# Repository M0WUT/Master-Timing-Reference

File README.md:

Artefacts: https://m0wut.github.io/Master-Timing-Reference/

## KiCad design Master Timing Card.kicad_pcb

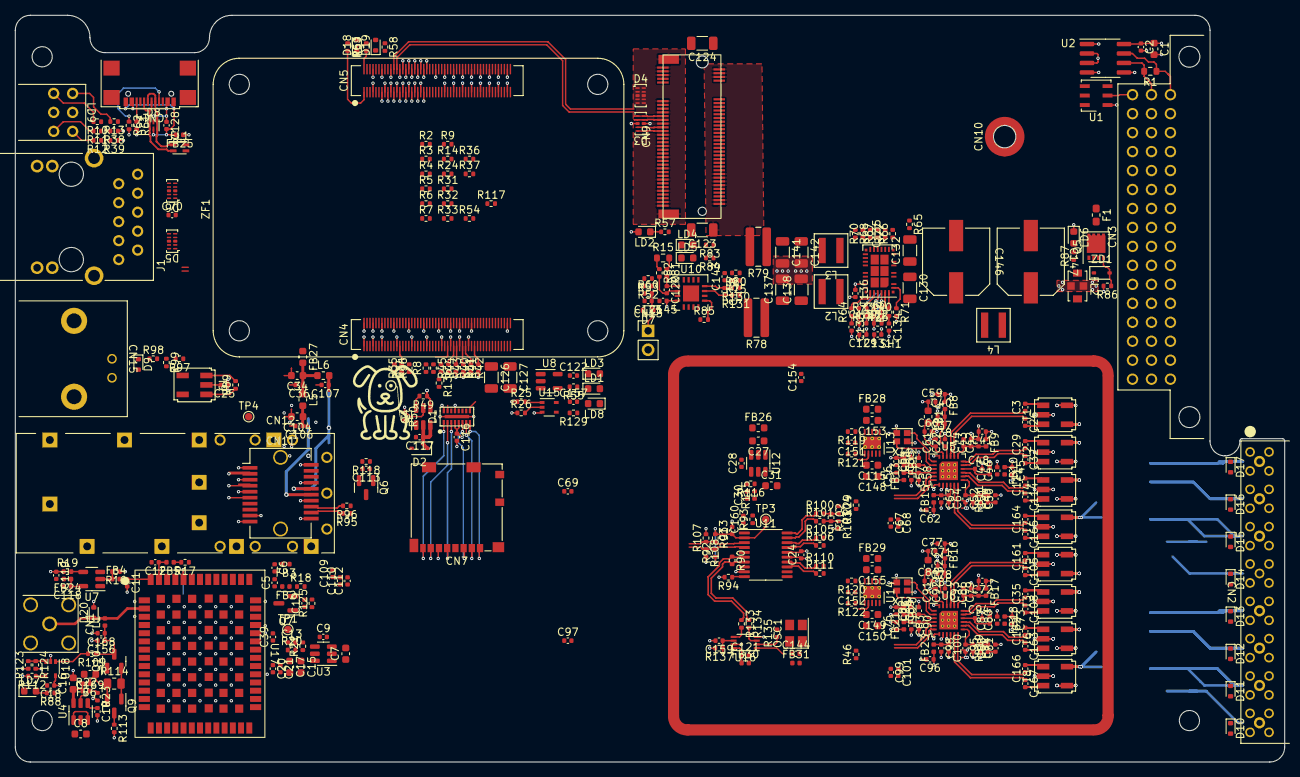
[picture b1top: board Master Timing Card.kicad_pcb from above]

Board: 4 copper layers, 170.0 x 100.0 mm, 418 parts (1 on the bottom side), 289 nets.

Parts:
C1, C7, C8, C15, C16, C17, C27, C31, C34, C104, C115, C148, C149, C150, C153, C155, C169: 10u; C_0603_1608Metric
C2, C3, C9, C10, C18, C19, C20, C21, C24, C25, C26, C28, C29, C32, C33, C35, C36, C38, C39, C40, C41, C43, C45, C47, C49, C51, C53, C55, C56, C58, C59, C61, C62, C64, C70, C71, C72, C73, C74, C75, C76, C77, C85, C86, C87, C88, C89, C90, C91, C96, C100, C105, C106, C107, C108, C111, C113, C114, C116, C117, C118, C121, C122, C125, C128, C135, C144, C145, C154, C156, C157, C159, C160, C161, C162, C163, C164, C165, C166, C167: 100n; C_0402_1005Metric
C5, C6, C11, C12, C67, C68, C69, C97, C99, C101, C109, C110, C112, C119: 100p; C_0402_1005Metric
C13, C30: 15p; C_0402_1005Metric
C22, C44, C48, C52, C92, C93, C94, C95, C168: 4n7; C_0402_1005Metric
C37, C42, C46, C50, C54, C57, C60, C63, C78, C79, C80, C81, C82, C83, C84, C98: 10u; C_0402_1005Metric
C120, C136, C143, C151, C152, C158: 1u; C_0402_1005Metric
C123, C124, C126, C127: 22u; C_1206_3216Metric
C129, C131: 10n; C_0402_1005Metric
C130, C132: 10u; C_1206_3216Metric
C133, C134: 220p; C_0402_1005Metric
C137, C138, C141, C142: 47u; C_1206_3216Metric
C139, C140: 10p; C_0402_1005Metric
C146, C147: 220u; Wurth_WCAP-HSG5_8x10.5mm_SM
CN1: CONSMA002-L-G; SMA_Linx_CONSMA002-L-G_Horizontal
CN2: Samtec GRF1-J-P-08-E-RA-TH1; Samtec_GRF1-J-P-08-E-RA-TH1
CN3: Amphenol 86093488613755E1LF; DIN41612_R_03x16_Receptacle_RA_Amphenol_86093488613755E1LF
CN4: Hirose_DF40C-100DS-0.4V
CN5: Hirose_DF40C-100DS-0.4V_pins-101-200
CN7: 104031-0811; microSD_HC_Molex_104031-0811
CN9: TE 1-2199230-6; TE_1-2199230-6
CN10: M2 x 2.5mm; Standoff_Wurth_9774025243R
CN11: UE75-A20-6000T; Amphenol_UE75-A20-6000T
CN12: U77-A1114-30L1; Amphenol_U77-A1114-30L1
CN13: Harwin M20-9990246; PinHeader_1x02_P2.54mm_Vertical
CN14: USB4110-GF-A; USB-C_GCT_USB4110-GF-A
CN15: 731385033; BNC_Molex_731385033
D1: ECLAMP2410P; Semtech_ECLAMP2410P
D2: 5V0; D_SOD-323
D3, D4, D5, D6: TPD4E05U06DQA
D7, D18, D19: 3V3; D_SOD-523
D8: USBLC6-2M6; TVS_ST_USBLC6-2M6
D9, D10, D11, D12, D13, D14, D15, D16, D17, D20: 5V0; D_SOD-523
F1: 1A; Fuse_0603_1608Metric_Pad1.05x0.95mm_HandSolder
FB2, FB3, FB4, FB5, FB6, FB8, FB9, FB10, FB11, FB12, FB13, FB15, FB16, FB17, FB18, FB19, FB20, FB21, FB23, FB24, FB25, FB30, FB31: 1k8; L_0402_1005Metric
FB14, FB22, FB26, FB27, FB28, FB29: 600R; L_0603_1608Metric
FL1: 90R; L_CommonMode_Wurth_WE-CNSW_0805
FL2: NFM31HK153R1H3; Murata_NFM31HK
H8: Logo_10mmx10mm
J1: Connector_RJ45_Magjack_Abracon_ARJM11D7-502-AB-EW2
L1: 47n; L_0402_1005Metric
L2, L3, L4: 2u2; Coilcraft_XEL4030
L5, L6: 1u0; L_0603_1608Metric
LAYOUT1, LAYOUT2, LAYOUT3: 2.7mm NPTH; MountingHole_2.7mm
LD1: Red; LED_0603_1608Metric
LD2, LD3, LD4, LD5, LD6, LD7, LD8: Green; LED_0603_1608Metric
LD9: WP130WCP_2EGW; Kingbright_WP130WCP_2EGW
OSC1: 10MHz; Crystal_SMD_3225-4Pin_3.2x2.5mm
Q4: onsemi FDC6330L; TSOT-23-6
Q5: TSM085P03CV RGG; PDFN33-8
Q6, Q7: DMN62D0U-7; SOT-23
Q9, Q10: MMBT2907A-7-F; SOT-23
R1: 120R; R_0603_1608Metric
R2, R3, R4, R31, R32, R35, R83, R84, R88, R117: 4k7; R_0402_1005Metric
R5, R6, R8, R9, R14, R24, R29, R33, R34, R36, R37, R46, R51, R58, R59, R60, R89, R90, R109, R136: 100R; R_0402_1005Metric
R7, R16, R17, R18, R19, R40, R41, R42, R43, R44, R45, R100, R101, R105, R106, R110, R111, R133, R134, R135: 33R; R_0402_1005Metric
R10, R11, R12, R13, R38, R39, R54, R55, R57, R113: 1k0; R_0402_1005Metric
R15: 150m; R_0603_1608Metric
R20, R22, R115, R124: 22k; R_0402_1005Metric
R21, R116: 13k; R_0402_1005Metric
R23: 7k5; R_0402_1005Metric
R25, R26, R49, R50, R66, R67, R86, R93, R112, R118, R123, R125, R129, R137: 10k; R_0402_1005Metric
R52, R53, R56, R63, R68, R70: 0R0; R_0402_1005Metric
R61, R62: 5k1; R_0402_1005Metric
R64, R69, R71, R76: 15k; R_0402_1005Metric
R65: 120k; R_0402_1005Metric
R72, R87: 47k; R_0402_1005Metric
R73: 160k; R_0402_1005Metric
R74: 30k; R_0402_1005Metric
R75, R80, R81, R82, R130, R131: 6R8; R_0402_1005Metric
R77, R85: 100k; R_0402_1005Metric
R78, R79: 56m; R_1020_2550Metric
R91, R92: 130R; R_0402_1005Metric
R94: 475R; R_0402_1005Metric
R95, R96: 10R; R_0402_1005Metric
R97, R98: 20R; R_0402_1005Metric
R99: 51R; R_0402_1005Metric
R102: 140R; R_0402_1005Metric
R103, R104: 180R; R_0402_1005Metric
R107, R108: 82R; R_0402_1005Metric
R114: 10R; R_0805_2012Metric
R119, R120: 330R; R_0402_1005Metric
R121, R122: 18k; R_0402_1005Metric
SH1: MS585-10F; Shield_Masach_MS585-10_58.2x49.4x4.7mm_SMD
T1, T2, T3, T4, T5, T6, T7, T8, T9: TC2-72T+; MiniCircuits_AT1521
TP1, TP3, TP4, TP5: TestPoint_Pad_D1.0mm
U1: DS2431P+; TSOC-6_3.76x3.94mm_P1.27mm
U2: Analog MAX3483ESA+; SOIC-8_3.9x4.9mm_P1.27mm
U3, U4, U12: TI TPS79301DBV; SOT-23-6
U5, U6: RC32504A000GNK#BB0; Renesas_QFN-24-1EP_4x4mm_P0.5mm_EP2.5x2.5mm_ThermalVias
U7, U8: SN74LVC1G125DBV; SOT-23-5
U9: Analog LT8650SEV#PBF; LQFN-32(28)-6EP_6x4mm_P0.5mm_EP1.1x1.33mm
U10: INA3221AIRGV; Texas_VQFN-16-1EP_RGV0016A
U11: SY75576LKY; TSSOP-20_4.4x6.5mm_P0.65mm
U13, U14: LT3045IDD#PBF; DFN-10-1EP_3x3mm_P0.5mm_EP1.65x2.38mm_ThermalVias
U15: SN74LVC1G02DCK; SOT-353_SC-70-5
U16: SN74LVC2G157DCU; VSSOP-8_2.3x2mm_P0.5mm
U17: ZED-F9T-10B; uBlox_ZED
U18: TLV7031DCK; SOT-353_SC-70-5
XT1, XT2: 60MHz; Crystal_SMD_2016-4Pin_2.0x1.6mm
ZD1: 15V; D_SOD-323
ZF1: CM4004016; Raspberry-Pi-4-Compute-Module

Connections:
0V: C1.2, C2.2, C5.2, C6.2, C7.2, C8.2, C9.2, C10.2, C11.2, C12.2, C15.2, C16.2, C17.2, C18.2, C19.2, C20.2, C21.2, C22.2, C24.2, C25.1, C27.2, C28.2, C31.2, C33.2, C34.2, C36.2, C37.2, C38.2, C39.2, C40.2, C41.2, C42.2, C43.2, C44.2, C45.2, C46.2, C47.2, C48.2, C49.2, C50.2, C51.2, C52.2, C53.2, C54.2, C55.2, C56.2, C57.2, C58.2, C59.2, C60.2, C61.2, C62.2, C63.2, C64.2, C67.2, C68.2, C69.2, C70.2, C71.2, C72.2, C73.2, C74.2, C75.2, C76.2, C77.2, C78.2, C79.2, C80.2, C81.2, C82.2, C83.2, C84.2, C85.2, C86.2, C87.2, C88.2, C89.2, C90.2, C91.2, C92.2, C93.2, C94.2, C95.2, C96.2, C97.2, C98.2, C99.2, C100.2, C101.2, C104.2, C106.2, C107.2, C109.2, C110.2, C112.2, C113.2, C115.2, C116.2, C117.2, C118.2, C119.2, C121.2, C122.2, C123.2, C124.2, C125.2, C126.2, C127.2, C129.2, C130.2, C131.2, C132.2, C133.2, C134.2, C135.2, C136.2, C137.2, C138.2, C141.2, C142.2, C144.2, C145.2, C146.2, C147.2, C148.2, C149.2, C150.2, C151.2, C152.2, C153.2, C154.2, C155.2, C156.2, C157.2, C159.2, C160.2, C168.2, C169.2, CN1.2 (Ext), CN2.SH1 (Ext), CN2.SH2 (Ext), CN2.SH3 (Ext), CN2.SH4 (Ext), CN2.SH5 (Ext), CN2.SH6 (Ext), CN2.SH7 (Ext), CN2.SH8 (Ext), CN3.a16, CN4.1 (GND), CN4.2 (GND), CN4.7 (GND), CN4.8 (GND), CN4.13 (GND), CN4.14 (GND), CN4.22 (GND), CN4.23 (GND), CN4.32 (GND), CN4.33 (GND), CN4.42 (GND), CN4.43 (GND), CN4.52 (GND), CN4.53 (GND), CN4.59 (GND), CN4.60 (GND), CN4.65 (GND), CN4.66 (GND), CN4.71 (GND), CN4.74 (GND), CN4.98 (GND), CN5.107 (GND), CN5.108 (GND), CN5.113 (GND), CN5.114 (GND), CN5.115 (CAM1_D0_N), CN5.117 (CAM1_D0_P), CN5.119 (GND), CN5.120 (GND), CN5.121 (CAM1_D1_N), CN5.123 (CAM1_D1_P), CN5.125 (GND), CN5.126 (GND), CN5.127 (CAM1_C_N), CN5.128 (CAM0_D0_N), CN5.129 (CAM1_C_P), CN5.130 (CAM0_D0_P), CN5.131 (GND), CN5.132 (GND), CN5.133 (CAM1_D2_N), CN5.134 (CAM0_D1_N), CN5.135 (CAM1_D2_P), CN5.136 (CAM0_D1_P), CN5.137 (GND), CN5.138 (GND), CN5.139 (CAM1_D3_N), CN5.140 (CAM0_C_N), CN5.141 (CAM1_D3_P), CN5.142 (CAM0_C_P), CN5.144 (GND), CN5.150 (GND), CN5.155 (GND), CN5.156 (GND), CN5.161 (GND), CN5.162 (GND), CN5.167 (GND), CN5.168 (GND), CN5.173 (GND), CN5.174 (GND), CN5.179 (GND), CN5.180 (GND), CN5.185 (GND), CN5.186 (GND), CN5.191 (GND), CN5.192 (GND), CN5.197 (GND), CN5.198 (GND), CN7.6 (VSS), CN7.9 (DET_B), CN7.10 (DET_A), CN7.11 (SHIELD), CN9.1 (GND), CN9.3 (GND), CN9.9 (GND), CN9.15 (GND), CN9.21 (GND), CN9.27 (GND), CN9.33 (GND), CN9.39 (GND), CN9.45 (GND), CN9.51 (GND), CN9.57 (GND), CN9.71 (GND), CN9.73 (GND), CN9.75 (GND), CN9.76 (MNT), CN10.1, CN11.1 (VeeT), CN11.9 (VeeR), CN11.10 (VeeR), CN11.11 (VeeR), CN11.14 (VeeR), CN11.17 (VeeT), CN11.20 (VeeT), CN12.1, CN13.2, CN14.SH (SHIELD), CN15.2 (Ext), D1.17 (0V), D2.2 (A), D3.3, D3.8, D4.3, D4.8, D5.3, D5.8, D6.3, D6.8, D7.2 (A), D9.2 (A), D10.2 (A), D11.2 (A), D12.2 (A), D13.2 (A), D14.2 (A), D15.2 (A), D16.2 (A), D17.2 (A), D18.2 (A), D19.2 (A), D20.2 (A), FB25.1, FL2.2, LD4.1 (K), LD5.1 (K), LD6.1 (K), LD7.1 (K), LD8.1 (K), LD9.2, LD9.5, OSC1.1 (GND), OSC1.2 (GND), Q4.1 (S1), Q6.2 (S), Q7.2 (S), R21.2, R23.2, R50.2, R52.1, R53.1, R56.2, R61.2, R62.2, R63.1, R66.2, R67.2, R70.2, R71.2, R74.2, R76.2, R86.2, R93.2, R94.2, R99.2, R103.2, R104.1, R107.2, R108.2, R113.2, R116.2, R118.2, R119.2, R120.2, R121.2, R122.2, R124.2, R125.2, R137.2, SH1.1, T1.2, T1.4, T2.2, T2.6, T3.2, T3.6, T4.2, T4.6, T5.2, T5.4, T6.2, T6.6, T7.2, T7.6, T8.2, T8.6, T9.6, U1.1 (GND), U2.5 (GND), U3.2 (GND), U4.2 (GND), U5.25 (VSS), U6.25 (VSS), U7.1 (~OE), U7.3 (-), U8.1 (~OE), U8.3 (-), U9.2 (GND), U9.10 (GND), U9.33 (GND), U9.34 (GND), U9.35 (GND), U9.36 (GND), U9.37 (GND), U9.38 (GND), U9.MNT, U10.3 (GND), U10.5 (A0), U10.17 (PAD), U11.9 (GND), U11.16 (GND), U12.2 (GND), U13.8 (GND), U13.11 (GND), U14.8 (GND), U14.11 (GND), U15.3 (0V), U16.4 (GND), U16.7 (~G), U17.1 (GND), U17.3 (GND), U17.12 (GND), U17.14 (GND), U17.32 (GND), U17.37 (GND), U17.38 (V_USB), U17.41 (GND), U17.48 (GND), U17.55 (MNT), U18.2 (V-), XT1.2, XT1.4, XT2.2, XT2.4
1V8: CN4.88 (+1.8v_(Output)), CN4.90 (+1.8v_(Output)), FB24.2
3V3: C1.1, C2.1, C18.1, C62.1, C96.1, C116.1, C122.1, C145.1, C157.1, CN4.78 (GPIO_VREF(1.8v/3.3v_Input)), D1.4 (RUP1), D1.5 (VDD), D1.13 (RUP3), FB15.1, FB23.1, FB27.1, FB30.2, FB31.2, LD1.2 (A), LD2.2 (A), LD3.2 (A), Q4.4 (S2), R2.1, R3.1, R4.1, R15.2, R25.1, R26.1, R31.1, R32.1, R35.1, R38.1, R39.1, R49.1, R77.1, R81.1, R85.1, R117.1, R123.1, U2.8 (VCC), U8.5 (+), U10.4 (VS), U10.16 (VPU), U15.5 (VCC), U18.5 (V+)
3V3_PCIE: C123.1, C124.1, C140.1, CN9.2 (3.3V), CN9.4 (3.3V), CN9.12 (3.3V), CN9.14 (3.3V), CN9.16 (3.3V), CN9.18 (3.3V), CN9.70 (3.3V), CN9.72 (3.3V), CN9.74 (3.3V), R72.1, R79.2, R80.1, R83.1
5V0_PI: C7.1, C8.1, C126.1, C127.1, C139.1, CN4.77 (+5v_(Input)), CN4.79 (+5v_(Input)), CN4.81 (+5v_(Input)), CN4.83 (+5v_(Input)), CN4.85 (+5v_(Input)), CN4.87 (+5v_(Input)), FB26.1, FB28.1, FB29.1, R73.1, R78.2, R84.1, R131.1, U3.1 (IN), U3.3 (EN), U4.1 (IN), U4.3 (EN)
/CM4 Interfaces/ETHA_N: CN4.10 (Ethernet_Pair0_N), D5.2, D5.9 (NC), J1.2
/CM4 Interfaces/ETHA_P: CN4.12 (Ethernet_Pair0_P), D5.1, D5.10 (NC), J1.1
/CM4 Interfaces/ETHB_N: CN4.6 (Ethernet_Pair1_N), D5.5, D5.6 (NC), J1.4
/CM4 Interfaces/ETHB_P: CN4.4 (Ethernet_Pair1_P), D5.4, D5.7 (NC), J1.3
/CM4 Interfaces/ETHC_N: CN4.9 (Ethernet_Pair2_N), D6.2, D6.9 (NC), J1.8
/CM4 Interfaces/ETHC_P: CN4.11 (Ethernet_Pair2_P), D6.1, D6.10 (NC), J1.7
/CM4 Interfaces/ETHD_N: CN4.5 (Ethernet_Pair3_N), D6.5, D6.6 (NC), J1.10
/CM4 Interfaces/ETHD_P: CN4.3 (Ethernet_Pair3_P), D6.4, D6.7 (NC), J1.9
/CM4 Interfaces/PTP_PPS: C119.1, CN4.16 (Ethernet_SYNC_IN(1.8v)), R19.1
/CM4 Interfaces/SD_CLK: D1.14 (CLK_OUT), R45.2
/CM4 Interfaces/SD_CMD: D1.11 (CMD_OUT), R44.2
/CM4 Interfaces/SD_DAT0: D1.15 (DAT0_OUT), R40.2
/CM4 Interfaces/SD_DAT1: D1.16 (DAT1_OUT), R41.2
/CM4 Interfaces/SD_DAT2: D1.9 (DAT2_OUT), R42.2
/CM4 Interfaces/SD_DAT3: D1.10 (DAT3_OUT), R43.2
/CM4 Interfaces/SD_PWR_ON: Q4.5 (G1), R50.1, R51.1
/CM4 Interfaces/VDD_SD: C117.1, CN7.4 (VDD), D2.1 (K), Q4.2 (D2), Q4.3 (D2)
/CM4 Interfaces/~ETH_ACT: CN4.15 (Ethernet_nLED3(3.3v)), J1.L2
/CM4 Interfaces/~ETH_LINK: CN4.17 (Ethernet_nLED2(3.3v)), J1.L4
/GPS/CLK_SEL: C159.1, R24.2, R137.1, U16.6 (~A/B)
/GPS/GNSS_CLK_M: C12.1, FB5.2, U17.53 (TIMEPULSE)
/GPS/GNSS_PPS: CN4.49 (GPIO18), R16.1
/GPS/GNSS_PPS_M: C11.1, FB4.2, U17.54 (TIMEPULSE2)
/GPS/GNSS_RESET: C19.1, Q7.1 (G), R14.2, R125.1
/GPS/GNSS_RX: CN4.34 (GPIO5), R18.2
/GPS/GNSS_TX: CN4.54 (GPIO4), FB3.1
/GPS/REF_CLK_N: R90.2, R134.1, U11.7 (IN2_N)
/GPS/REF_CLK_P: R90.1, R133.1, U11.6 (IN2_P)
/GPS/~ANT_SHORT: R112.2, U17.6 (ANT_SHORT_N)
/PLL and SFP/CLKA_N: R101.1, U11.19 (CLKA_N)
/PLL and SFP/CLKA_P: R100.1, U11.20 (CLKA_P)
/PLL and SFP/CLKB_N: R106.1, U11.17 (CLKB_N)
/PLL and SFP/CLKB_P: R105.1, U11.18 (CLKB_P)
/PLL and SFP/CLKC_N: R111.1, U11.13 (CLKC_N)
/PLL and SFP/CLKC_P: R110.1, U11.14 (CLKC_P)
/PLL and SFP/CLKD_N: R89.2, T9.1, U11.11 (CLKD_N)
/PLL and SFP/CLKD_P: R89.1, T9.3, U11.12 (CLKD_P)
/PLL and SFP/CLK_SEL: C160.1, R93.1, R136.2, U11.1 (SEL)
/PLL and SFP/Frequency Synthesiser 1/1V8_PLL: C40.1, C41.1, C45.1, C49.1, C53.1, C56.1, C59.1, C115.1, C148.1, FB8.1, FB9.1, FB10.1, FB11.1, FB12.1, FB13.1, FB14.1, U13.9 (OUTS), U13.10 (OUT)
/PLL and SFP/Frequency Synthesiser 1/1V8_VDDA: C60.1, C61.1, FB14.2, U5.23 (VDDA)
/PLL and SFP/Frequency Synthesiser 1/1V8_VDDO0: C22.1, C37.1, C38.1, FB8.2, U5.22 (VDDO0)
/PLL and SFP/Frequency Synthesiser 1/1V8_VDDO1: C42.1, C43.1, C44.1, FB9.2, U5.19 (VDDO1)
/PLL and SFP/Frequency Synthesiser 1/1V8_VDDO2: C46.1, C47.1, C48.1, FB10.2, U5.16 (VDDO2)
/PLL and SFP/Frequency Synthesiser 1/1V8_VDDO3: C50.1, C51.1, C52.1, FB11.2, U5.13 (VDDO3)
/PLL and SFP/Frequency Synthesiser 1/1V8_VDDREF: C57.1, C58.1, FB13.2, U5.4 (VDDREF)
/PLL and SFP/Frequency Synthesiser 1/1V8_VDDXO: C54.1, C55.1, FB12.2, U5.3 (VDDXO)
/PLL and SFP/Frequency Synthesiser 1/3V3_VDDD: C63.1, C64.1, FB15.2, U5.10 (VDDD)
/PLL and SFP/Frequency Synthesiser 1/RF1_N: C3.1, U5.21 (OUT0_N)
/PLL and SFP/Frequency Synthesiser 1/RF1_P: C26.1, U5.20 (OUT0_P)
/PLL and SFP/Frequency Synthesiser 1/RF2_N: C32.1, U5.17 (OUT1_N)
/PLL and SFP/Frequency Synthesiser 1/RF2_P: C29.1, U5.18 (OUT1_P)
/PLL and SFP/Frequency Synthesiser 1/RF3_N: C114.1, U5.14 (OUT2_N)
/PLL and SFP/Frequency Synthesiser 1/RF3_P: C111.1, U5.15 (OUT2_P)
/PLL and SFP/Frequency Synthesiser 1/RF4_N: C165.1, U5.11 (OUT3_N)
/PLL and SFP/Frequency Synthesiser 1/RF4_P: C164.1, U5.12 (OUT3_P)
/PLL and SFP/Frequency Synthesiser 1/VIN: C153.1, FB28.2, U13.1 (IN), U13.2 (IN), U13.3 (EN/UV), U13.6 (PGFB)
/PLL and SFP/Frequency Synthesiser 1/~PLL_LOCK_OD: R25.2, R29.2, U15.1
/PLL and SFP/Frequency Synthesiser 2/1V8_PLL: C71.1, C72.1, C73.1, C74.1, C75.1, C76.1, C77.1, C149.1, C150.1, FB16.1, FB17.1, FB18.1, FB19.1, FB20.1, FB21.1, FB22.1, U14.9 (OUTS), U14.10 (OUT)
/PLL and SFP/Frequency Synthesiser 2/1V8_VDDA: C84.1, C91.1, FB22.2, U6.23 (VDDA)
/PLL and SFP/Frequency Synthesiser 2/1V8_VDDO0: C78.1, C85.1, C92.1, FB16.2, U6.22 (VDDO0)
/PLL and SFP/Frequency Synthesiser 2/1V8_VDDO1: C79.1, C86.1, C93.1, FB17.2, U6.19 (VDDO1)
/PLL and SFP/Frequency Synthesiser 2/1V8_VDDO2: C80.1, C87.1, C94.1, FB18.2, U6.16 (VDDO2)
/PLL and SFP/Frequency Synthesiser 2/1V8_VDDO3: C81.1, C88.1, C95.1, FB19.2, U6.13 (VDDO3)
/PLL and SFP/Frequency Synthesiser 2/1V8_VDDREF: C83.1, C90.1, FB21.2, U6.4 (VDDREF)
/PLL and SFP/Frequency Synthesiser 2/1V8_VDDXO: C82.1, C89.1, FB20.2, U6.3 (VDDXO)
/PLL and SFP/Frequency Synthesiser 2/3V3_VDDD: C98.1, C100.1, FB23.2, U6.10 (VDDD)
/PLL and SFP/Frequency Synthesiser 2/RF1_N: C161.1, U6.21 (OUT0_N)
/PLL and SFP/Frequency Synthesiser 2/RF1_P: C105.1, U6.20 (OUT0_P)
/PLL and SFP/Frequency Synthesiser 2/RF2_N: C108.1, U6.17 (OUT1_N)
/PLL and SFP/Frequency Synthesiser 2/RF2_P: C35.1, U6.18 (OUT1_P)
/PLL and SFP/Frequency Synthesiser 2/RF3_N: C163.1, U6.14 (OUT2_N)
/PLL and SFP/Frequency Synthesiser 2/RF3_P: C162.1, U6.15 (OUT2_P)
/PLL and SFP/Frequency Synthesiser 2/RF4_N: C167.1, U6.11 (OUT3_N)
/PLL and SFP/Frequency Synthesiser 2/RF4_P: C166.1, U6.12 (OUT3_P)
/PLL and SFP/Frequency Synthesiser 2/VIN: C155.1, FB29.2, U14.1 (IN), U14.2 (IN), U14.3 (EN/UV), U14.6 (PGFB)
/PLL and SFP/Frequency Synthesiser 2/~PLL_LOCK_OD: R26.2, R46.2, U15.2
/PLL and SFP/PLL1_CLK_N: R106.2, U5.6 (CLKIN_N)
/PLL and SFP/PLL1_CLK_P: R105.2, U5.5 (CLKIN_P)
/PLL and SFP/PLL1_SCL: C67.1, CN4.56 (GPIO3), R3.2, U5.8 (SCLK)
/PLL and SFP/PLL1_SDA: C68.1, CN4.58 (GPIO2), R2.2, U5.9 (SDIO)
/PLL and SFP/PLL2_CLK_N: R111.2, U6.6 (CLKIN_N)
/PLL and SFP/PLL2_CLK_P: R110.2, U6.5 (CLKIN_P)
/PLL and SFP/PLL2_SCL: C99.1, C110.1, CN4.37 (GPIO7), CN11.5 (MOD_DEF1/SCL), R32.2, U6.8 (SCLK), U10.6 (SCL)
/PLL and SFP/PLL2_SDA: C101.1, C112.1, CN4.30 (GPIO6), CN11.4 (MOD_DEF2/SDA), R31.2, U6.9 (SDIO), U10.7 (SDA)
/PLL and SFP/PLL_LOCK: CN4.27 (GPIO20), R129.2, U15.4
/PLL and SFP/PLL_OE: C69.1, C97.1, R5.2, U5.7 (OE/~CS), U6.7 (OE/~CS)
/PLL and SFP/REFCLK_R_N: CN11.13 (RD+), R96.2
/PLL and SFP/REFCLK_R_P: CN11.12 (RD-), R95.2
/PLL and SFP/SFP_LOS_OD: CN4.25 (GPIO21), CN11.8 (LOS), R35.2
/PLL and SFP/SFP_REFCLK_N: R92.2, R96.1, R108.1, U11.4 (IN1_N)
/PLL and SFP/SFP_REFCLK_P: R91.2, R95.1, R107.1, U11.3 (IN1_P)
/PLL and SFP/SFP_TX_DISABLE: C113.1, Q6.1 (G), R36.2, R118.1
/PLL and SFP/SFP_TX_FAULT_OD: CN4.40 (GPIO9), CN11.2 (TX_FAULT), R4.2
/PLL and SFP/SFP_TX_N: CN11.19 (TD-), R101.2, R102.2, R103.1
/PLL and SFP/SFP_TX_P: CN11.18 (TD+), R100.2, R102.1, R104.2
/PLL and SFP/VDD_MUX: C24.1, C30.1, C31.1, C33.1, C154.1, R91.1, R92.1, R115.1, TP3.1, U11.2 (VDDIN), U11.15 (VDD), U12.6 (OUT)
/PLL and SFP/~SFP_PRESENT: C109.1, CN4.39 (GPIO8), CN11.6 (MOD_DEF0/GND), R117.2
/Pi CM4 - GPIO/3V3_PCIE_EN: C135.1, R8.2, R67.1, U9.12 (EN2)
/Pi CM4 - GPIO/3V3_SENSE_N: C120.1, R81.2, U10.1 (IN3-)
/Pi CM4 - GPIO/3V3_SENSE_P: C120.2, R82.2, U10.2 (IN3+)
/Pi CM4 - GPIO/COMMS_GREEN: R6.1, R11.1
/Pi CM4 - GPIO/COMMS_RED: R9.1, R10.1
/Pi CM4 - GPIO/PCIE_PWR_GOOD: CN4.45 (GPIO24), R77.2, U9.15 (PG2)
/Pi CM4 - GPIO/PWR_CRITICAL: CN4.47 (GPIO23), R85.2, U10.9 (CRITICAL)
/Pi CM4 - GPIO/STATUS_GREEN: R12.1, R33.1
/Pi CM4 - GPIO/STATUS_RED: R13.1, R34.1
/Pi CM4 - HPIO/D_N: CN5.103 (USB2_N), FL1.2
/Pi CM4 - HPIO/D_P: CN5.105 (USB2_P), FL1.4
/Pi CM4 - HPIO/PCIE_PER0_N: CN5.118 (PCIe_RX_N), CN9.41 (PERn0), D3.1, D3.10 (NC)
/Pi CM4 - HPIO/PCIE_PER0_P: CN5.116 (PCIe_RX_P), CN9.43 (PERp0), D3.2, D3.9 (NC)
/Pi CM4 - HPIO/PCIE_PET0_N: CN5.124 (PCIe_TX_N), CN9.47 (PETn0), D3.4, D3.7 (NC)
/Pi CM4 - HPIO/PCIE_PET0_P: CN5.122 (PCIe_TX_P), CN9.49 (PETp0), D3.5, D3.6 (NC)
/Pi CM4 - HPIO/PCIE_REFCLK_N: CN5.112 (PCIe_CLK_N), CN9.53 (REFCLKn), D4.5, D4.6 (NC)
/Pi CM4 - HPIO/PCIE_REFCLK_P: CN5.110 (PCIe_CLK_P), CN9.55 (REFCLKp), D4.4, D4.7 (NC)
/Pi CM4 - HPIO/USB_N: CN14.A7 (DN1), CN14.B7 (DN2), D8.3, D8.4, FL1.1
/Pi CM4 - HPIO/USB_P: CN14.A6 (DP1), CN14.B6 (DP2), D8.1, D8.6, FL1.3
/Pi CM4 - HPIO/~PCIE_CLK_REQ: CN5.102 (PCIe_CLK_nREQ), R59.1
/Pi CM4 - HPIO/~PCIE_RST: CN9.50 (~PERST), D19.1 (K), R58.2
/Power Supplies/5V0_SENSE_N: C158.2, R131.2, U10.11 (IN1-)
/Power Supplies/5V0_SENSE_P: C158.1, R130.2, U10.12 (IN1+)
/Power Supplies/12V_DCDC: C130.1, C132.1, C146.1, L4.2, R65.1, U9.4 (VIN1), U9.5 (VIN1), U9.7 (VIN2), U9.8 (VIN2)
/Power Supplies/12V_F: F1.2, Q5.5, Q5.6, Q5.7, Q5.8
/Power Supplies/12V_FILT: C147.1, FL2.3, L4.1
/Power Supplies/12V_PROT: FL2.1, Q5.1, Q5.2, Q5.3, R87.1, ZD1.1 (K)
/Power Supplies/PCIE_SENSE_N: C143.2, R80.2, U10.14 (IN2-)
/Power Supplies/PCIE_SENSE_P: C143.1, R75.2, U10.15 (IN2+)
/Power Supplies/SW1: L2.1, U9.22 (SW1), U9.23 (SW1)
/Power Supplies/SW2: L3.1, U9.19 (SW2), U9.20 (SW2)
/RF1: CN2.1 (In), D17.1 (K), T1.6
/RF2: CN2.2 (In), D16.1 (K), T2.4
/RF3: CN2.3 (In), D15.1 (K), T4.4
/RF4: CN2.4 (In), D14.1 (K), T7.4
/RF5: CN2.5 (In), D13.1 (K), T5.6
/RF6: CN2.6 (In), D12.1 (K), T3.4
/RF7: CN2.7 (In), D11.1 (K), T6.4
/RF8: CN2.8 (In), D10.1 (K), T8.4
/RS485_A: CN3.b1, R1.2, U2.6 (A)
/RS485_B: CN3.a1, R1.1, U2.7 (B)
/RS485_RX: CN4.51 (GPIO15), U2.1 (RO)
/RS485_TX: R7.2, U2.4 (DI)
/RS485_~R/W: R37.2, U2.2 (~RE), U2.3 (DE)
unnamed: C3.2, T1.3
unnamed: C25.2, T9.2
unnamed: C26.2, T1.1
unnamed: C29.2, T2.3
unnamed: C32.2, T2.1
unnamed: C34.1, C36.1, FB27.2, L5.1, L6.1
unnamed: C35.2, T3.3
unnamed: C70.1, J1.5, J1.6
unnamed: C105.2, T5.1
unnamed: C108.2, T3.1
unnamed: C111.2, T4.3
unnamed: C114.2, T4.1
unnamed: C128.1, CN14.A4 (VBUS), CN14.A9 (VBUS), CN14.B4 (VBUS), CN14.B9 (VBUS), D8.5
unnamed: C128.2, CN14.A1 (GND), CN14.A12 (GND), CN14.B1 (GND), CN14.B12 (GND), D8.2, FB25.2
unnamed: C133.1, R64.1
unnamed: C134.1, R69.1
unnamed: C137.1, C138.1, L2.2, R78.1, R130.1
unnamed: C141.1, C142.1, L3.2, R75.1, R79.1
unnamed: C161.2, T5.3
unnamed: C162.2, T6.3
unnamed: C163.2, T6.1
unnamed: C164.2, T7.3
unnamed: C165.2, T7.1
unnamed: C166.2, T8.3
unnamed: C167.2, T8.1
unnamed: CN1.1 (In), D20.1 (K), L1.2, U17.2 (RF_IN)
unnamed: CN4.91 (BT_nDisable), R52.2
unnamed: CN4.20 (EEPROM_nWP), R56.1
unnamed: CN4.21 (PI_nLED_Activity), R54.2
unnamed: CN4.89 (WiFi_nDisable), R53.2
unnamed: CN4.95 (nPI_LED_PWR), U8.2
unnamed: CN4.93 (nRPIBOOT), R60.1
unnamed: CN4.57 (SD_CLK), R45.1
unnamed: CN4.62 (SD_CMD), R44.1
unnamed: CN4.63 (SD_DAT0), R40.1
unnamed: CN4.67 (SD_DAT1), R41.1
unnamed: CN4.69 (SD_DAT2), R42.1
unnamed: CN4.61 (SD_DAT3), R43.1
unnamed: CN4.75 (SD_PWR_ON), R51.2
unnamed: CN4.84 (+3.3v_(Output)), CN4.86 (+3.3v_(Output)), R15.1, R82.1
unnamed: CN4.44 (GPIO10), R6.2
unnamed: CN4.38 (GPIO11), R9.2
unnamed: CN4.31 (GPIO12), R33.2
unnamed: CN4.28 (GPIO13), R34.2
unnamed: CN4.55 (GPIO14), R7.1
unnamed: CN4.29 (GPIO16), R5.1
unnamed: CN4.50 (GPIO17), R37.1
unnamed: CN4.26 (GPIO19), R36.1
unnamed: CN4.46 (GPIO22), R8.1
unnamed: CN4.41 (GPIO25), R14.1
unnamed: CN4.24 (GPIO26), R24.1
unnamed: CN4.48 (GPIO27), R136.1
unnamed: CN5.109 (PCIe_nRST), R58.1
unnamed: CN5.101 (USB_OTG_ID), R63.2
unnamed: CN7.5 (CLK), D1.3 (CLK_IN)
unnamed: CN7.3 (CMD), D1.6 (CMD_IN)
unnamed: CN7.7 (DAT0), D1.2 (DAT0_IN)
unnamed: CN7.8 (DAT1), D1.1 (DAT1_IN)
unnamed: CN7.1 (DAT2), D1.8 (DAT2_IN)
unnamed: CN7.2 (DAT3/CD), D1.7 (DAT3_IN)
unnamed: CN9.52 (~CLKREQ), D18.1 (K), R59.2
unnamed: CN9.10 (~LED1), R57.2
unnamed: CN11.7 (RATE_SELECT), TP4.1
unnamed: CN11.3 (TX_DISABLE), Q6.3 (D)
unnamed: C104.1, C106.1, CN11.15 (VccR), L5.2
unnamed: C107.1, CN11.16 (VccT), L6.2
unnamed: C125.1, CN13.1, D7.1 (K), R60.2
unnamed: CN14.A5 (CC1), R62.1
unnamed: CN14.B5 (CC2), R61.1
unnamed: CN15.1 (In), D9.1 (K), R98.2
unnamed: FB2.1, R18.1
unnamed: FB4.1, R16.2, U7.2
unnamed: FB5.1, R17.2
unnamed: J1.L1, R39.2
unnamed: J1.L3, R38.2
unnamed: LD1.1 (K), R55.1
unnamed: LD2.1 (K), R57.1
unnamed: LD3.1 (K), R54.1
unnamed: LD4.2 (A), R83.2
unnamed: LD5.2 (A), R84.2
unnamed: LD6.2 (A), R87.2
unnamed: LD7.2 (A), R88.2
unnamed: LD8.2 (A), R129.1
unnamed: LD9.1, R13.2
unnamed: LD9.3, R12.2
unnamed: LD9.4, R10.2
unnamed: LD9.6, R11.2
unnamed: OSC1.3 (OUT), R135.2
unnamed: C144.1, FB31.1, OSC1.4 (VCC)
unnamed: Q4.6 (D1), R49.2
unnamed: Q7.3 (D), U17.49 (~RESET)
unnamed: C169.1, FB6.1, Q9.2 (E), R114.1
unnamed: Q9.3 (C), Q10.1 (B), R113.1
unnamed: C156.1, C168.1, L1.1, Q10.3 (C), R109.1
unnamed: Q9.1 (B), Q10.2 (E), R114.2
unnamed: R19.2, U7.4
unnamed: R55.2, U8.4
unnamed: R97.1, T9.4
unnamed: R97.2, R98.1, R99.1
unnamed: R112.1, U18.4
unnamed: CN3.c1, U1.2 (IO)
unnamed: C13.2, R20.2, R21.1, U3.5 (FB)
unnamed: C9.1, U3.4 (NR)
unnamed: R22.2, R23.1, U4.5 (FB)
unnamed: C10.1, U4.4 (NR)
unnamed: C16.1, FB6.2, R22.1, R88.1, U4.6 (OUT)
unnamed: R29.1, U5.24 (LOCK)
unnamed: U5.1 (XIN/REF), XT1.1
unnamed: U5.2 (XOUT), XT1.3
unnamed: R46.1, U6.24 (LOCK)
unnamed: U6.1 (XIN/REF), XT2.1
unnamed: U6.2 (XOUT), XT2.3
unnamed: C118.1, FB24.1, U7.5 (+)
unnamed: R65.2, R66.1, U9.11 (EN1)
unnamed: C139.2, R73.2, R74.1, U9.28 (FB1)
unnamed: C140.2, R72.2, R76.1, U9.31 (FB2)
unnamed: R71.1, U9.1 (RT)
unnamed: C129.1, U9.29 (SS1)
unnamed: C131.1, U9.30 (SS2)
unnamed: R68.2, R70.1, U9.16 (SYNC)
unnamed: R64.2, U9.27 (VC1)
unnamed: R69.2, U9.32 (VC2)
unnamed: C136.1, R68.1, U9.25 (VCC)
unnamed: R94.1, U11.10 (IREF)
unnamed: C27.1, FB26.2, U12.1 (IN), U12.3 (EN)
unnamed: C30.2, R115.2, R116.1, U12.5 (FB)
unnamed: C28.1, U12.4 (NR)
unnamed: R119.1, U13.5 (ILIM)
unnamed: C151.1, R121.1, U13.7 (SET)
unnamed: R120.1, U14.5 (ILIM)
unnamed: C152.1, R122.1, U14.7 (SET)
unnamed: R17.1, U16.1 (A)
unnamed: R135.1, U16.2 (B)
unnamed: C121.1, FB30.1, U16.8 (VCC)
unnamed: R133.2, U16.5 (Y)
unnamed: R134.2, U16.3 (~Y)
unnamed: C6.1, FB3.2, U17.43 (RXD/SPI_MOSI)
unnamed: C5.1, FB2.2, U17.42 (TXD/SPI_MISO)
unnamed: C13.1, C15.1, C17.1, C20.1, C21.1, C39.1, R20.1, TP1.1, U3.6 (OUT), U17.33 (VCC), U17.34 (VCC), U17.36 (V_BCKP)
unnamed: TP5.1, U17.50 (~SAFEBOOT)
unnamed: R109.2, U18.1 (+)
unnamed: R123.2, R124.1, U18.3 (-)
unnamed: Q5.4, R86.1, ZD1.2 (A)

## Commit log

2023-11-06 Added demo Github actions
2023-11-06 gets Kicad installed on actions
2023-11-06 fixed typo
2023-11-07 added README
2023-11-08 removed web folder
2023-11-11 added M0WUT libraries
2023-11-13 Moved to installing from requirements.txt
2023-11-13 Discovered kikit only works on local folder
2023-11-13 Fixed working directory issues
2023-11-15 Added ibom
2023-11-15 whitespace is good
2023-11-19 Added M.2 SSD
2023-11-20 Added SFP connector
2023-11-20 Tried changing library path
2023-11-21 test
2023-11-21 typo
2023-11-26 Added ESD and tided up PSU
2023-12-02 started on power
2023-12-04 Added power supply
2023-12-09 Schematic mostly done
2023-12-10 schematic complete
2023-12-14 Moved to preferred library
2023-12-15 Started placement
2023-12-16 moving to discrete GPS recevier
2023-12-16 Moved to discrete GPS
2023-12-19 initial placement
2023-12-19 stuff
2023-12-30 layout progress
2024-01-01 updated github workflow
2024-01-01 less than 100 tracks to go!
2024-01-01 getting there
2024-01-07 committing before attempting scripting
2024-01-21 Fixed connector offsets
2024-01-21 Think complete - apart from 12V connection
    Removed accidential step file
2024-04-14 released version
2024-04-27 Attempting to use Docker container
2024-04-27 take 2
2024-04-29 should work now?
2024-05-01 speedup
2024-05-01 testing with second pcb
2024-05-01 Removed some old files from testing
2026-05-09 removed test files
